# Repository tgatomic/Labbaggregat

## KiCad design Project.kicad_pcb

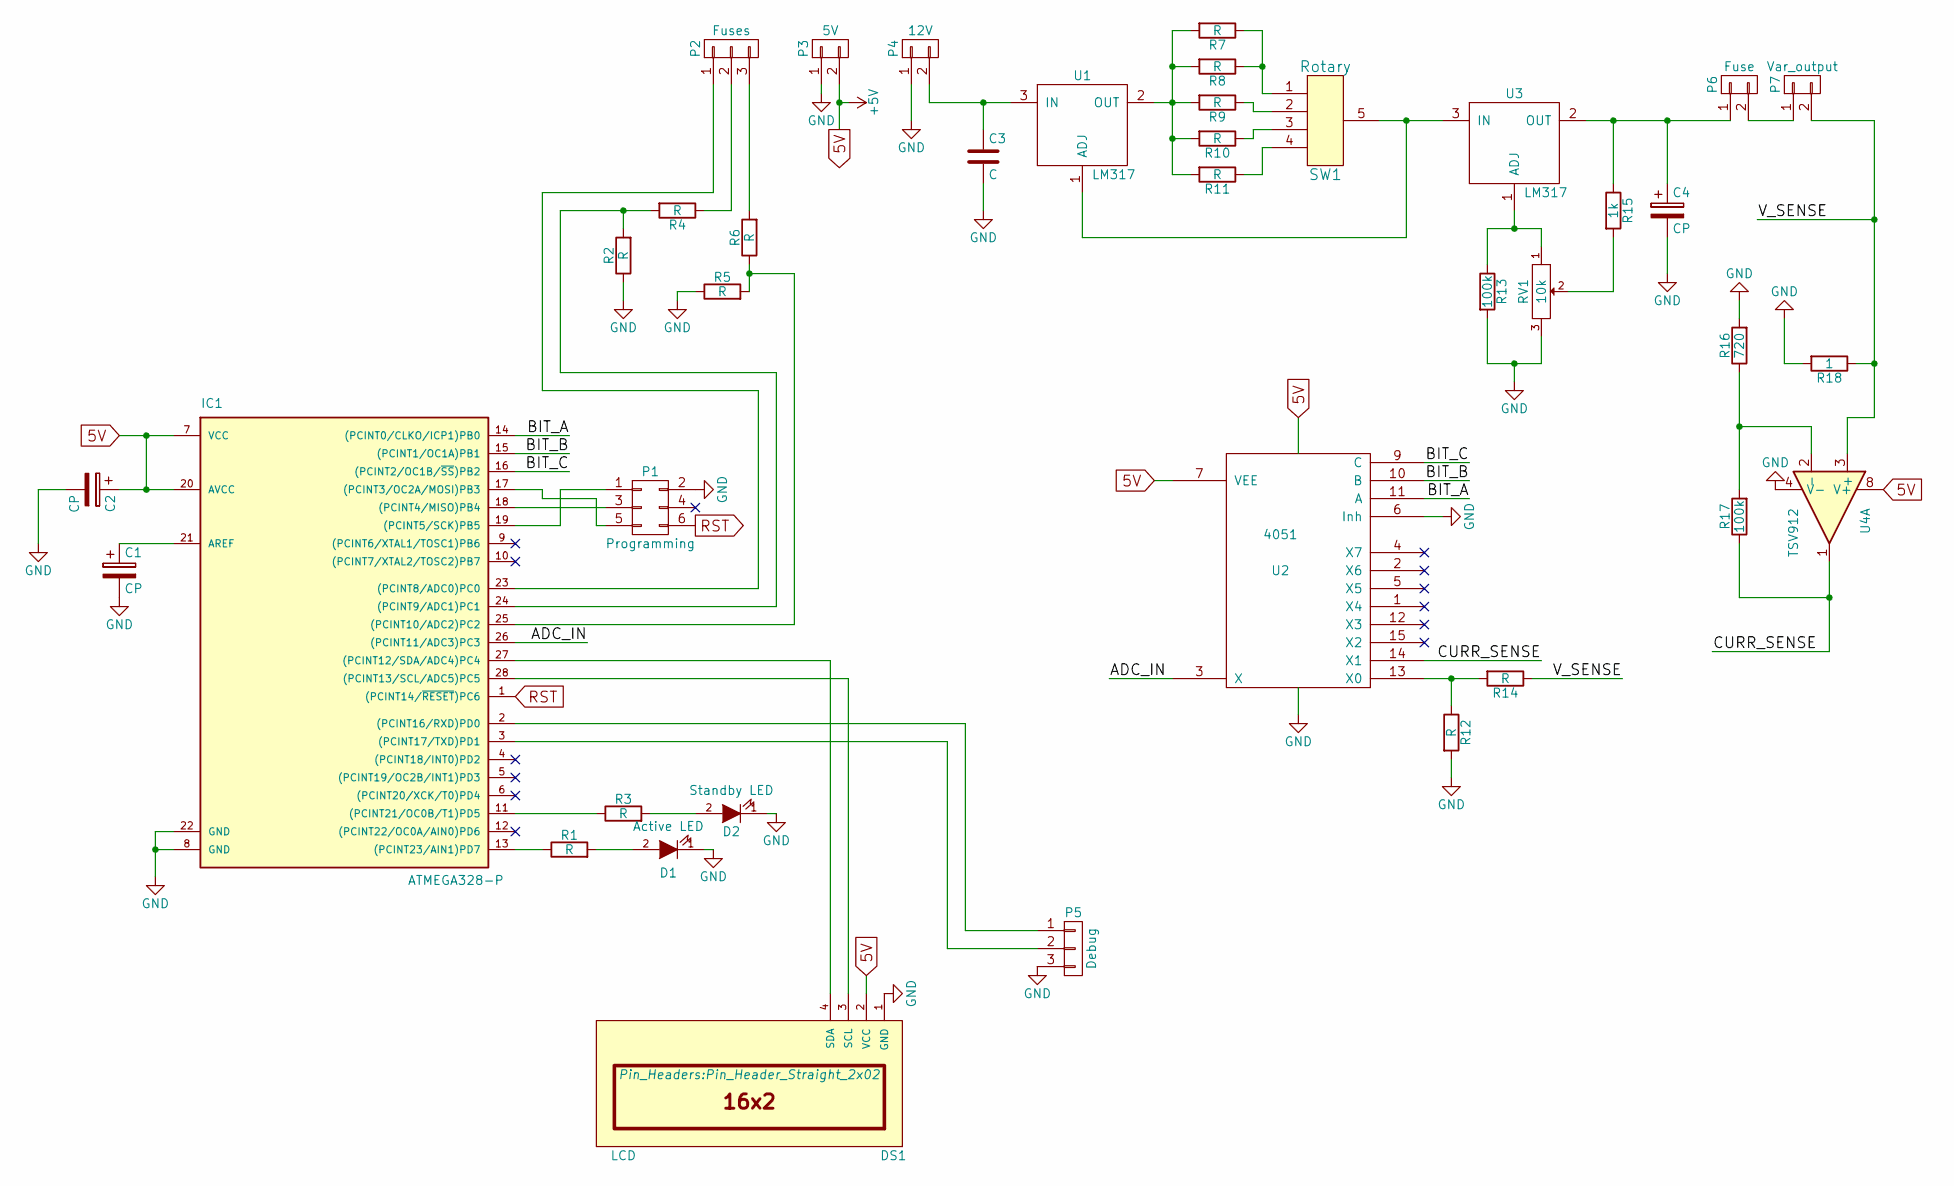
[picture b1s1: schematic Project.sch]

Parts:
C1, C2, C4: CP; C_0805_HandSoldering
C3: C; C_0805_HandSoldering
D1: Active LED; Pin_Header_Straight_1x02_Pitch1.27mm
D2: Standby LED; Pin_Header_Straight_1x02_Pitch1.27mm
DS1: LCD; Pin_Header_Straight_2x02
IC1: ATMEGA328-P; QFP80P900X900X120-32N
P1: Programming; Pin_Header_Straight_2x03
P2: Fuses; Pin_Header_Straight_1x03
P3: 5V; Pin_Header_Straight_1x02
P4: 12V; Pin_Header_Straight_1x02
P5: Debug; Pin_Header_Straight_1x03
P6: Fuse; Pin_Header_Straight_1x02
P7: Var_output; Pin_Header_Straight_1x02
R1, R2, R3, R4, R5, R6, R7, R8, R9, R10, R11, R12, R14: R; R_0805_HandSoldering
R13, R17: 100k; R_0805_HandSoldering
R15: 1k; R_0805_HandSoldering
R16: 720; R_0805_HandSoldering
R18: 1; R_0805_HandSoldering
RV1: 10k; Pin_Header_Straight_1x03
SW1: Rotary; Pin_Header_Angled_2x03_Pitch1.27mm
U1, U3: LM317; TO-220_Neutral123_Vertical
U2: 4051; TSSOP_16; Part number 74HC4051PW-Q100,11
U4: TSV912; SOP65P490X110-8N

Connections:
5V: C2.1, DS1.2 (VCC), IC1.7 (VCC), IC1.20 (AVCC), P3.2, U2.7 (VEE), U2.8 (VSS), U4.8 (V+)
/ADC_IN: IC1.26 ((PCINT11/ADC3)PC3), U2.3 (X)
/BIT_A: IC1.14 ((PCINT0/CLKO/ICP1)PB0), U2.11 (A)
/BIT_B: IC1.15 ((PCINT1/OC1A)PB1), U2.10 (B)
/BIT_C: IC1.16 ((PCINT2/OC1B/~SS~)PB2), U2.9 (C)
/CURR_SENSE: R17.1, U2.14 (X1), U4.1
/V_SENSE: P7.2, R14.1, R18.1, U4.3 (+)
GND: C1.2, C2.2, C3.2, C4.2, D1.1 (K), D2.1 (K), DS1.1 (GND), IC1.8 (GND), IC1.22 (GND), P1.2, P3.1, P4.1, P5.3, R2.1, R5.1, R12.2, R13.2, R16.2, R18.2, RV1.3, U2.6 (Inh), U2.16 (VDD), U4.4 (V-)
unnamed: C1.1, IC1.21 (AREF)
unnamed: C3.1, P4.2, U1.3 (IN)
unnamed: C4.1, P6.1, R15.1, U3.2 (OUT)
unnamed: D1.2 (A), R1.2
unnamed: D2.2 (A), R3.2
unnamed: DS1.3 (SCL), IC1.28 ((PCINT13/SCL/ADC5)PC5)
unnamed: DS1.4 (SDA), IC1.27 ((PCINT12/SDA/ADC4)PC4)
unnamed: IC1.2 ((PCINT16/RXD)PD0), P5.1
unnamed: IC1.3 ((PCINT17/TXD)PD1), P5.2
unnamed: IC1.11 ((PCINT21/OC0B/T1)PD5), R3.1
unnamed: IC1.13 ((PCINT23/AIN1)PD7), R1.1
unnamed: IC1.17 ((PCINT3/OC2A/MOSI)PB3), P1.5
unnamed: IC1.18 ((PCINT4/MISO)PB4), P1.3
unnamed: IC1.19 ((PCINT5/SCK)PB5), P1.1
unnamed: IC1.23 ((PCINT8/ADC0)PC0), P2.1
unnamed: IC1.24 ((PCINT9/ADC1)PC1), R2.2, R4.2
unnamed: IC1.25 ((PCINT10/ADC2)PC2), R5.2, R6.1
unnamed: P2.2, R4.1
unnamed: P2.3, R6.2
unnamed: P6.2, P7.1
unnamed: R7.1, R8.1, SW1.1
unnamed: R9.1, SW1.2
unnamed: R10.1, SW1.3
unnamed: R7.2, R8.2, R9.2, R10.2, R11.2, U1.2 (OUT)
unnamed: R11.1, SW1.4
unnamed: R12.1, R14.2, U2.13 (X0)
unnamed: R13.1, RV1.1, U3.1 (ADJ)
unnamed: R15.2, RV1.2
unnamed: R16.1, R17.2, U4.2 (-)
unnamed: SW1.5, U1.1 (ADJ), U3.3 (IN)
RST: IC1.1 ((PCINT14/~RESET~)PC6), P1.6

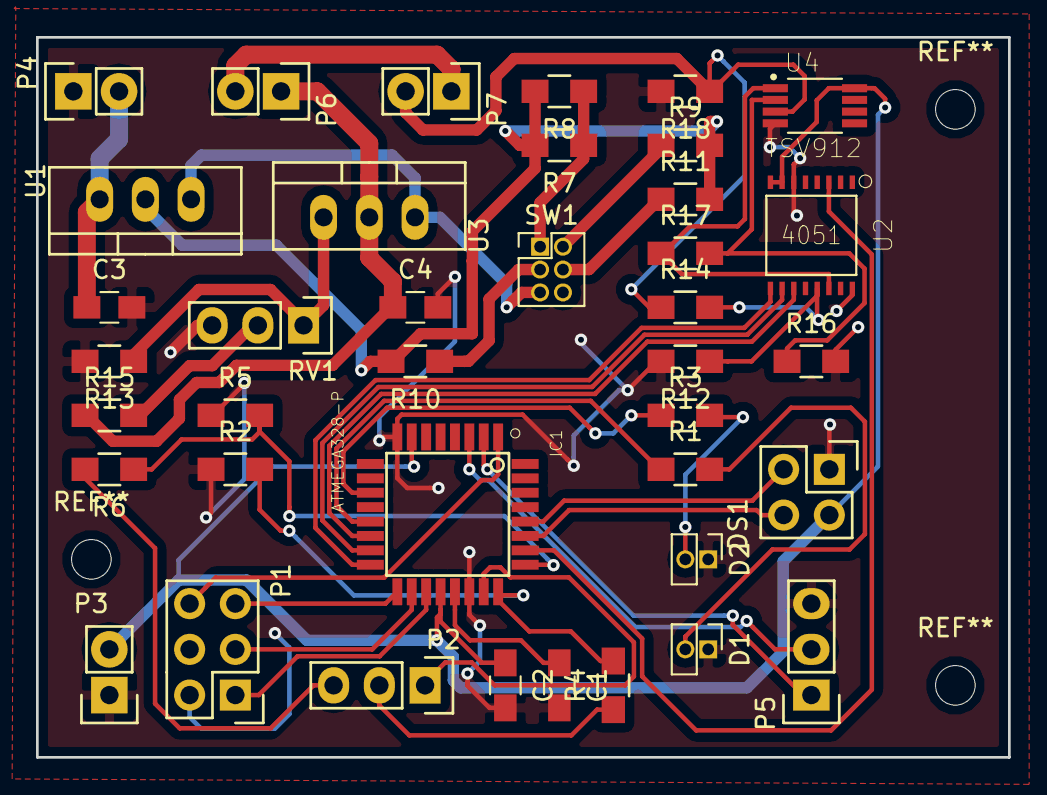
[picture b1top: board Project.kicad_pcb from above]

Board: 2 copper layers, 54.0 x 40.0 mm, 39 parts (0 on the bottom side), 39 nets.

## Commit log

2017-02-09 First version finished
